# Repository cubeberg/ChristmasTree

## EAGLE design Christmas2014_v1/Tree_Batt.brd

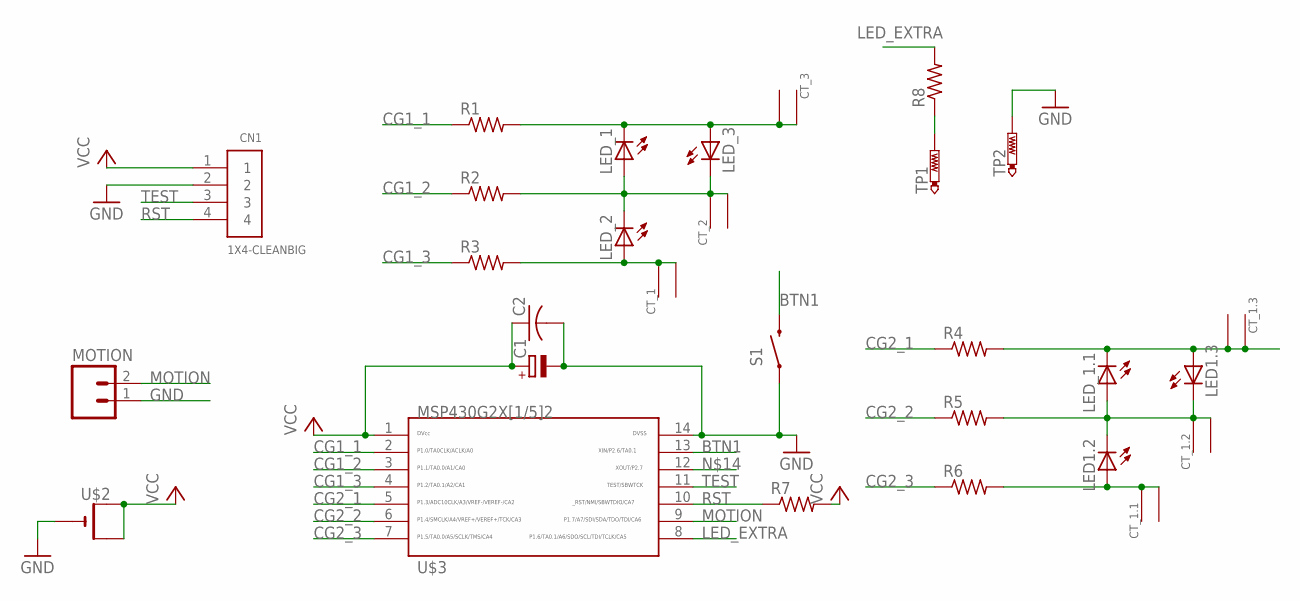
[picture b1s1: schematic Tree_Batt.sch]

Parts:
C1: CPOL-EUE2,5-6E; E2,5-6E
C2: C-US025-024X044; C025-024X044
CN1: 1X4-CLEANBIG; 1X04-CLEANBIG
CT_1, CT_1.1, CT_1.2, CT_1.3, CT_2, CT_3: SMD_PAD; 5X5TREEPAD
LED1.2, LED1.3: LEDLED_CLEAN_EDGE; 1X02_NO_SILK
LED_1, LED_1.1, LED_2, LED_3: LEDLED_CLEAN_EDGE; 1X02_NO_SILK
MOTION: M021X02_NO_SILK; 1X02_NO_SILK
R1, R2, R3, R4, R5, R6, R7, R8: R-US_0204/7; 0204/7
S1: SWITCH-MOMENTARY-2-SMD-1101NE; TACTILE-SWITCH-1101NE
TP1, TP2: PTR1PAD1-13; P1-13
U$2: CR2032SMT; CR2032-SMD
U$3: G2X[1/5]2---PW14; PW14

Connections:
BTN1: S1.P$2 (2), U$3.13
CG1_1: R1.1, U$3.2
CG1_2: R2.1, U$3.3
CG1_3: R3.1, U$3.4
CG2_1: R4.1, U$3.5
CG2_2: R5.1, U$3.6
CG2_3: R6.1, U$3.7
GND: C1.-, C2.2, CN1.2, MOTION.1, S1.P$1 (1), TP2.TP, U$2.-, U$3.14
LED_EXTRA: R8.2, U$3.8
MOTION: MOTION.2, U$3.9
unnamed: CT_1.P$1, CT_1.P$2, LED_2.1 (A), R3.2
unnamed: CT_2.P$1, CT_2.P$2, LED_1.1 (A), LED_2.2 (C), LED_3.2 (C), R2.2
unnamed: CT_3.P$1, CT_3.P$2, LED_1.2 (C), LED_3.1 (A), R1.2
unnamed: R8.1, TP1.TP
unnamed: CT_1.2.P$1, CT_1.2.P$2, LED1.2.2 (C), LED1.3.2 (C), LED_1.1.1 (A), R5.2
unnamed: CT_1.3.P$1, CT_1.3.P$2, LED1.3.1 (A), LED_1.1.2 (C), R4.2
unnamed: CT_1.1.P$1, CT_1.1.P$2, LED1.2.1 (A), R6.2
RST: CN1.4, R7.1, U$3.10
TEST: CN1.3, U$3.11
VCC: C1.+, C2.1, CN1.1, R7.2, U$2.+$1 (+), U$2.+$2 (+1), U$3.1

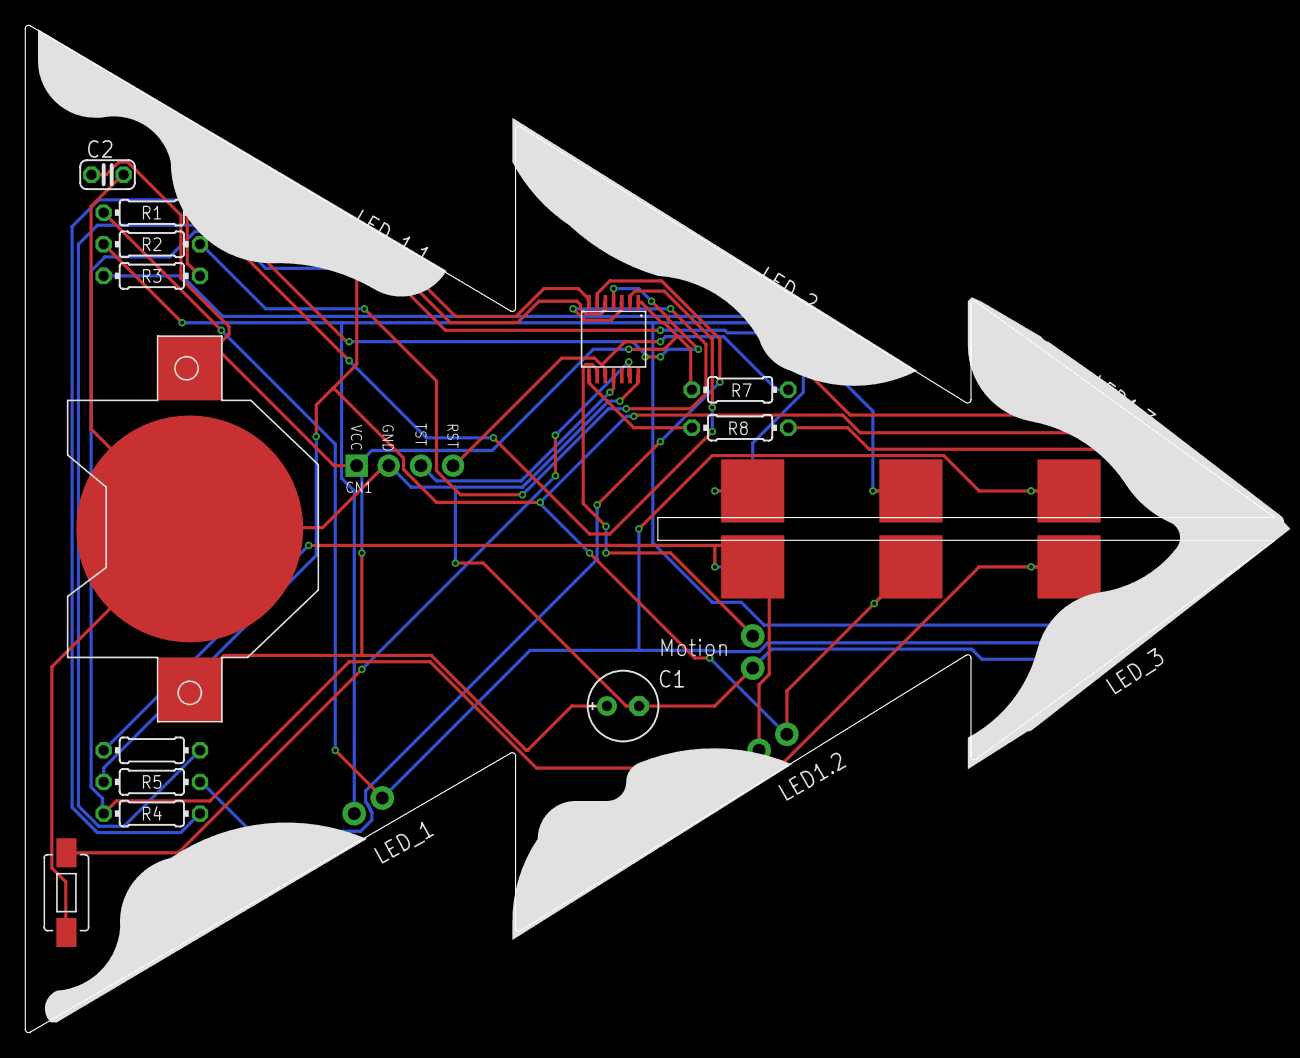
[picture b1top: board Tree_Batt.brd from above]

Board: 2 copper layers, 98.8 x 79.6 mm, 42 parts (0 on the bottom side), 20 nets.

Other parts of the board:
U$1: TREE_SHAPE
U$4: TREE_SNOW
U$5, U$6, U$7, U$8, U$9, U$10, U$11, U$12, U$13, U$14, U$15: SNOWFLAKE_1

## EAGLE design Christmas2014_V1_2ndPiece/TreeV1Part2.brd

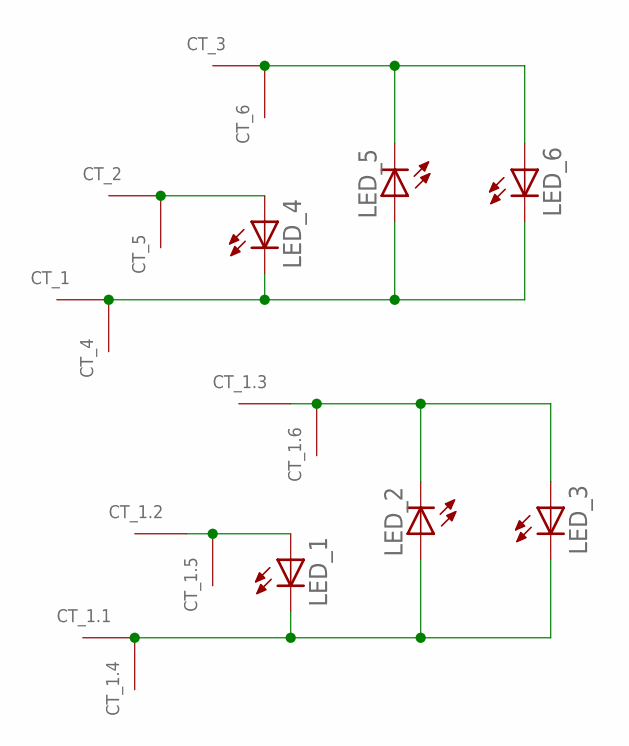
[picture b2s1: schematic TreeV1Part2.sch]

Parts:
CT_1, CT_1.1, CT_1.2, CT_1.3, CT_1.4, CT_1.5, CT_1.6, CT_2, CT_3, CT_4, CT_5, CT_6: SMD_PAD_SINGLE; 5X5TREEPAD_SINGLE
LED_1, LED_2, LED_3, LED_4, LED_5, LED_6: LEDLED_CLEAN_EDGE; 1X02_NO_SILK

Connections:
unnamed: CT_3.P$1, CT_6.P$1, LED_5.2 (C), LED_6.1 (A)
unnamed: CT_1.P$1, CT_4.P$1, LED_4.2 (C), LED_5.1 (A), LED_6.2 (C)
unnamed: CT_1.3.P$1, CT_1.6.P$1, LED_2.2 (C), LED_3.1 (A)
unnamed: CT_2.P$1, CT_5.P$1, LED_4.1 (A)
unnamed: CT_1.1.P$1, CT_1.4.P$1, LED_1.2 (C), LED_2.1 (A), LED_3.2 (C)
unnamed: CT_1.2.P$1, CT_1.5.P$1, LED_1.1 (A)

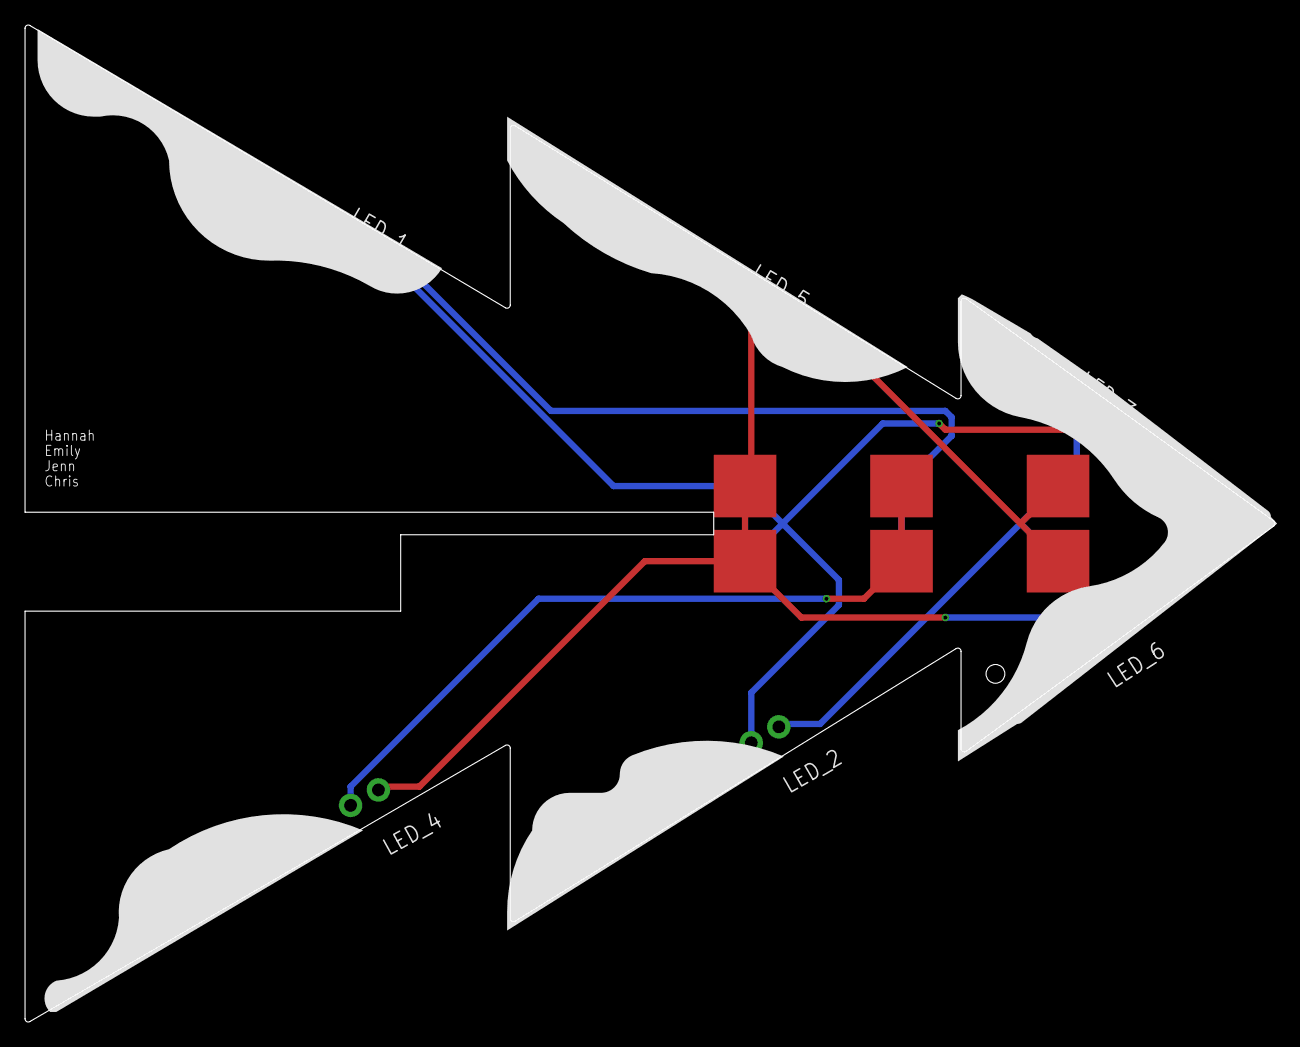
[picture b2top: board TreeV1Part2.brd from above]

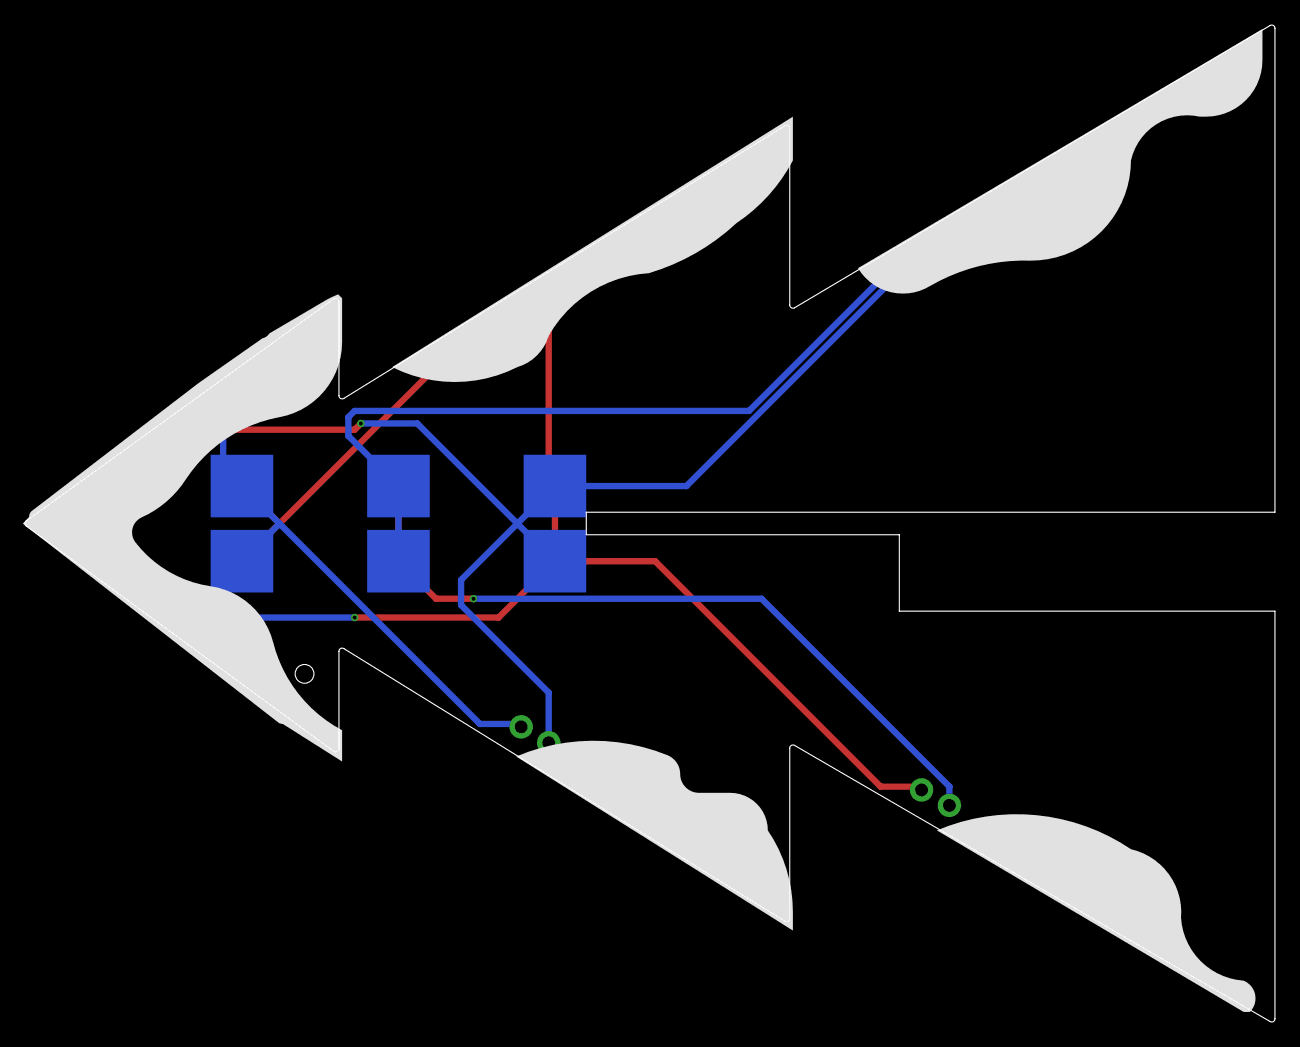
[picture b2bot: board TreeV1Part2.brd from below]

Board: 2 copper layers, 99.8 x 79.6 mm, 33 parts (6 on the bottom side), 6 nets.

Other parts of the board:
U$1: TREE_NOBATT
U$2: TREE_SNOW
U$3, U$4, U$5, U$6, U$7, U$8, U$9, U$10, U$11, U$12, U$13, U$14, U$15: SNOWFLAKE_1

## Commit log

2014-12-10 Adding code and eagle files

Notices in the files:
parts and their libraries:
Sparkfun: Licensing: CC v3.0 Share-Alike You are welcome to use this library for commercial purposes.
